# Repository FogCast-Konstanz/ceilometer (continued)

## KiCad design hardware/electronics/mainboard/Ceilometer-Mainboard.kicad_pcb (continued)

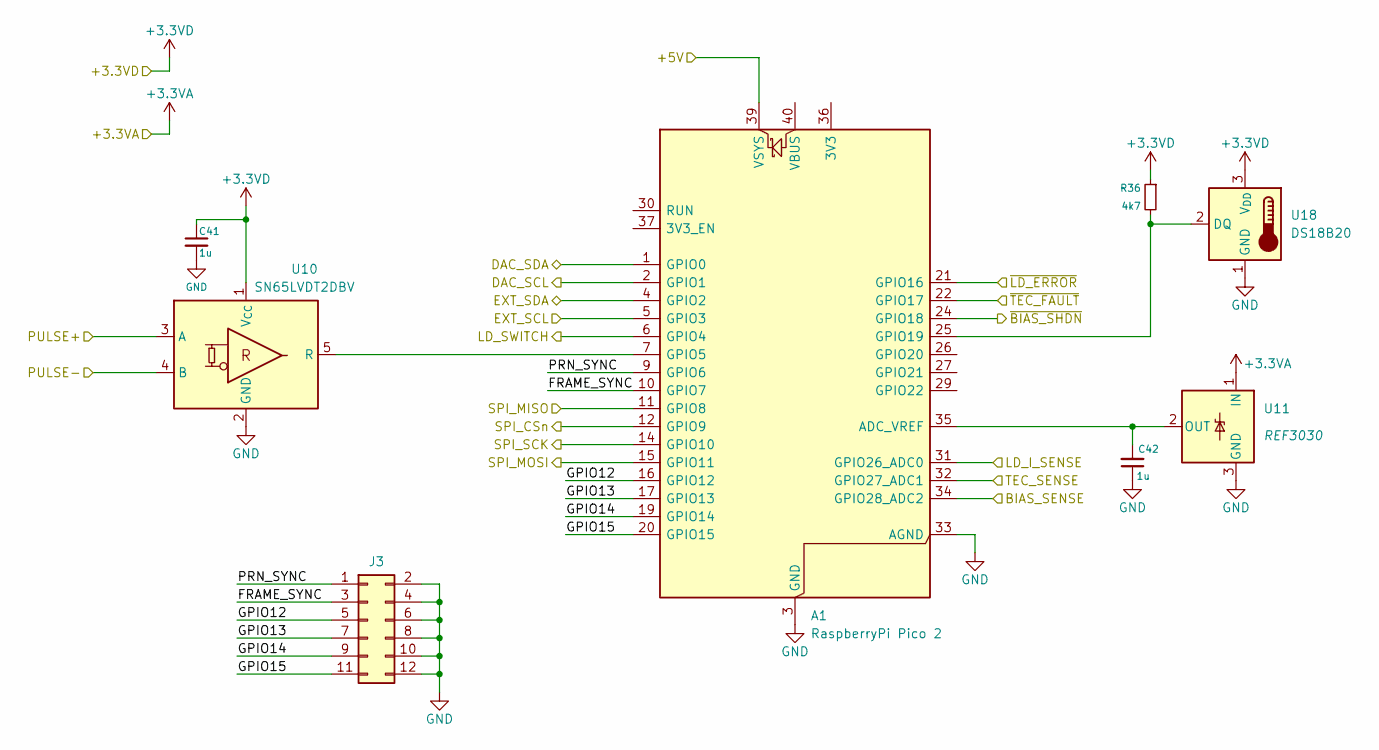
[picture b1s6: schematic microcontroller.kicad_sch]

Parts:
A1: RaspberryPi Pico 2; RaspberryPi_Pico_Common_SMD; MPN RP2350-Plus
C41, C42: 1u; C_0402_1005Metric; Voltage 35V; MPN C1005X5R1V105K050BE
J3: Conn_02x06_Odd_Even; PinHeader_2x06_P2.54mm_Vertical
R36: 4k7; R_0402_1005Metric; MPN ERA-2AED472X
U10: SN65LVDT2DBV; SOT-23-5; MPN SN65LVDT2DBV
U11: REF3030; SOT-23; MPN REF3030AIDBZT
U18: DS18B20; PinHeader_1x03_P2.54mm_Vertical; MPN DS18B20

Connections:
+3.3VA: U11.1 (IN); also elsewhere on the board
+3.3VD: C41.1, R36.1, U10.1 (V_{CC}), U18.3 (V_{DD}); also elsewhere on the board
+5V: A1.39 (VSYS); also elsewhere on the board
/Laser Driver/LD_DAC_SCL: A1.2 (GPIO1); also elsewhere on the board
/Laser Driver/LD_DAC_SDA: A1.1 (GPIO0); also elsewhere on the board
/Laser Driver/LD_SWITCH: A1.6 (GPIO4); also elsewhere on the board
/Laser Driver/V_I_LD_SENSE: A1.31 (GPIO26_ADC0); also elsewhere on the board
/Laser Driver/~LD_ERROR: A1.21 (GPIO16); also elsewhere on the board
/Microcontroller/BIAS_SENSE: A1.34 (GPIO28_ADC2); also elsewhere on the board
/Microcontroller/EXT_SCL: A1.5 (GPIO3); also elsewhere on the board
/Microcontroller/EXT_SDA: A1.4 (GPIO2); also elsewhere on the board
/Microcontroller/FRAME_SYNC: A1.10 (GPIO7), J3.3
/Microcontroller/GPIO12: A1.16 (GPIO12), J3.5
/Microcontroller/GPIO13: A1.17 (GPIO13), J3.7
/Microcontroller/GPIO14: A1.19 (GPIO14), J3.9
/Microcontroller/GPIO15: A1.20 (GPIO15), J3.11
/Microcontroller/PRN_SYNC: A1.9 (GPIO6), J3.1
/Microcontroller/PULSE+: U10.3 (A); also elsewhere on the board
/Microcontroller/PULSE-: U10.4 (B); also elsewhere on the board
/Microcontroller/SPI_CSn: A1.12 (GPIO9); also elsewhere on the board
/Microcontroller/SPI_MISO: A1.11 (GPIO8); also elsewhere on the board
/Microcontroller/SPI_MOSI: A1.15 (GPIO11); also elsewhere on the board
/Microcontroller/SPI_SCK: A1.14 (GPIO10); also elsewhere on the board
/Microcontroller/TEC_SENSE: A1.32 (GPIO27_ADC1); also elsewhere on the board
/Microcontroller/~BIAS_SHDN: A1.24 (GPIO18); also elsewhere on the board
/Microcontroller/~TEC_FAULT: A1.22 (GPIO17); also elsewhere on the board
GND: A1.3 (GND), A1.8 (GND), A1.13 (GND), A1.18 (GND), A1.23 (GND), A1.28 (GND), A1.33 (AGND), A1.38 (GND), C41.2, C42.1, J3.2, J3.4, J3.6, J3.8, J3.10, J3.12, U10.2 (GND), U11.3 (GND), U18.1 (GND); also elsewhere on the board
unnamed: A1.35 (ADC_VREF), C42.2, U11.2 (OUT)
unnamed: A1.7 (GPIO5), U10.5 (R)
unnamed: A1.25 (GPIO19), R36.2, U18.2 (DQ)

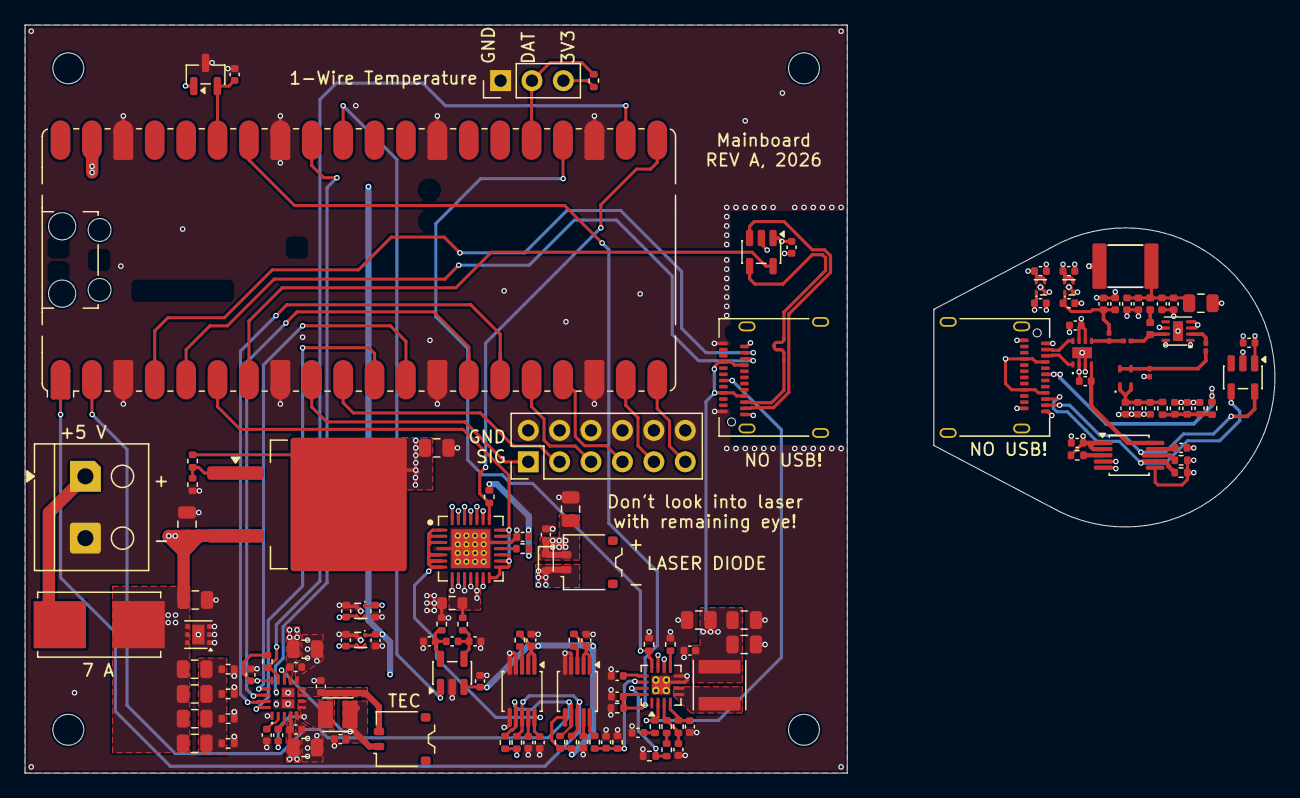
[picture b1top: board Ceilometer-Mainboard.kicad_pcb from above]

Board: 4 copper layers, 101.1 x 60.5 mm, 144 parts (0 on the bottom side), 79 nets.

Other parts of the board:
B1, B2: Board

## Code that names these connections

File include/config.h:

#pragma once
#include <stdint.h>
#define PRN_LENGTH 1023u
#define CAPTURE_MAX_FRAMES 16u
#define CAPTURE_MAX_SAMPLES (PRN_LENGTH * CAPTURE_MAX_FRAMES + 1u)
#define TX_WORDS PRN_LENGTH /* 32 exact frames, no 1023->1024 padding */
#define CHIP_CYCLES 10u /* Allowed chip-period quantum in clk_sys cycles. */
#define DEFAULT_CHIP_HZ 10000000u
#ifndef SYSTEM_KHZ
#define SYSTEM_KHZ 500000u
#endif
#define PIN_LD_SDA 0u
#define PIN_LD_SCL 1u
#define PIN_RX_SDA 2u
#define PIN_RX_SCL 3u
#define PIN_LD_GATE 4u
#define PIN_SIPM 5u
#define PIN_CHIP_SYNC 6u
#define PIN_FRAME_SYNC 7u
#define PIN_SPI_MISO 8u
#define PIN_SPI_CS 9u
#define PIN_SPI_SCK 10u
#define PIN_SPI_MOSI 11u
#define PIN_TEST_PULSE 12u
#define PIN_TEST_PRN 13u
#define PIN_LD_ERROR 16u
#define PIN_TEC_SWEN 17u /* schematic misleadingly calls this ~TEC_FAULT */
#define PIN_BIAS_ENABLE 18u
#define PIN_ONEWIRE 19u
#define PIN_LD_ADC 26u
#define PIN_TEC_ADC 27u
#define PIN_BIAS_ADC 28u /* LT3571 MON current, NOT divided bias voltage */
#define PWM_COUNTER_SLICE 2u
#define PWM_TIMER_SLICE 3u
#define I2C_LD_ADDRESS 0x4cu
#define I2C_BIAS_ADDRESS 0x4eu /* AD5693R A0 is address bit 1, bit 0 is fixed zero */
#define I2C_THRESHOLD_ADDRESS 0x4eu
#define I2C_TEMPERATURE_ADDRESS 0x48u
